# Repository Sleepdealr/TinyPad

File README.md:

# Tinypad 4x3 Macropad

Small & cheap 4x3 macropad with space for 2 rotary encoders

Has been prototyped once and small changes has been made

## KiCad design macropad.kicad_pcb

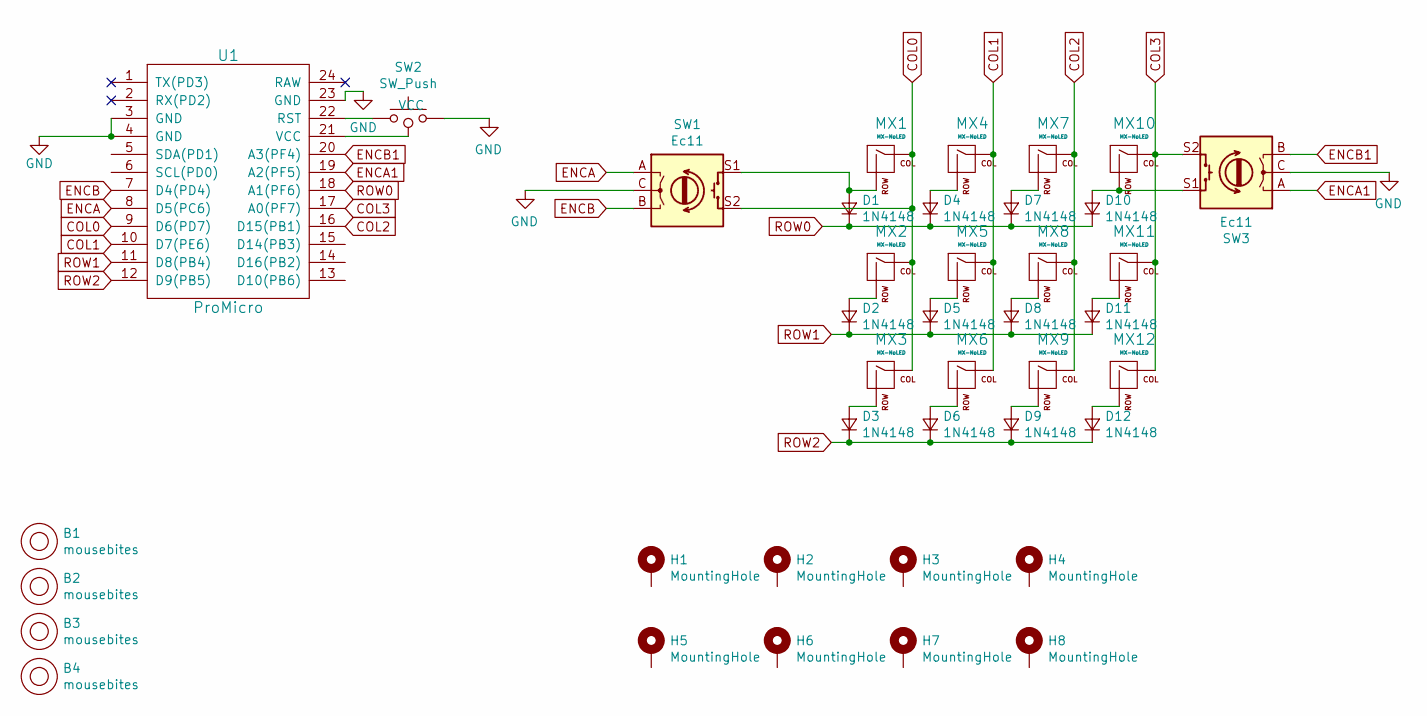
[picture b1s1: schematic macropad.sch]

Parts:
B1, B2, B3, B4: mousebites; breakaway-mousebites
D1, D2, D3, D4, D5, D6, D7, D8, D9, D10, D11, D12: 1N4148; D_DO-35_SOD27_P7.62mm_Horizontal
H1, H2, H3, H4, H5, H6, H7, H8: MountingHole; MountingHole_2.2mm_M2_Pad
MX1, MX2, MX3, MX4, MX5, MX6, MX7, MX8, MX9, MX10, MX11, MX12: MX-NoLED; MXOnly-1U-NoLED
SW1, SW3: Ec11; RotaryEncoder_Alps_EC11E-Switch_Vertical_H20mm
SW2: SW_Push; TACT_SWITCH_TVBP06
U1: ProMicro; ArduinoProMicro

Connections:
COL0: MX1.1 (COL), MX2.1 (COL), MX3.1 (COL), SW1.S2, U1.9 (D6(PD7))
COL1: MX4.1 (COL), MX5.1 (COL), MX6.1 (COL), U1.10 (D7(PE6))
COL2: MX7.1 (COL), MX8.1 (COL), MX9.1 (COL), U1.16 (D15(PB1))
COL3: MX10.1 (COL), MX11.1 (COL), MX12.1 (COL), SW3.S2, U1.17 (A0(PF7))
ENCA: SW1.A, U1.8 (D5(PC6))
ENCA1: SW3.A, U1.19 (A2(PF5))
ENCB: SW1.B, U1.7 (D4(PD4))
ENCB1: SW3.B, U1.20 (A3(PF4))
GND: SW1.C, SW2.1, SW3.C, U1.3 (GND), U1.4 (GND), U1.23 (GND)
unnamed: D1.2 (A), MX1.2 (ROW), SW1.S1
unnamed: D2.2 (A), MX2.2 (ROW)
unnamed: D3.2 (A), MX3.2 (ROW)
unnamed: D4.2 (A), MX4.2 (ROW)
unnamed: D5.2 (A), MX5.2 (ROW)
unnamed: D6.2 (A), MX6.2 (ROW)
unnamed: D7.2 (A), MX7.2 (ROW)
unnamed: D8.2 (A), MX8.2 (ROW)
unnamed: D9.2 (A), MX9.2 (ROW)
unnamed: D10.2 (A), MX10.2 (ROW), SW3.S1
unnamed: D11.2 (A), MX11.2 (ROW)
unnamed: D12.2 (A), MX12.2 (ROW)
unnamed: SW2.2, U1.22 (RST)
ROW0: D1.1 (K), D4.1 (K), D7.1 (K), D10.1 (K), U1.18 (A1(PF6))
ROW1: D2.1 (K), D5.1 (K), D8.1 (K), D11.1 (K), U1.11 (D8(PB4))
ROW2: D3.1 (K), D6.1 (K), D9.1 (K), D12.1 (K), U1.12 (D9(PB5))
VCC: U1.21 (VCC)

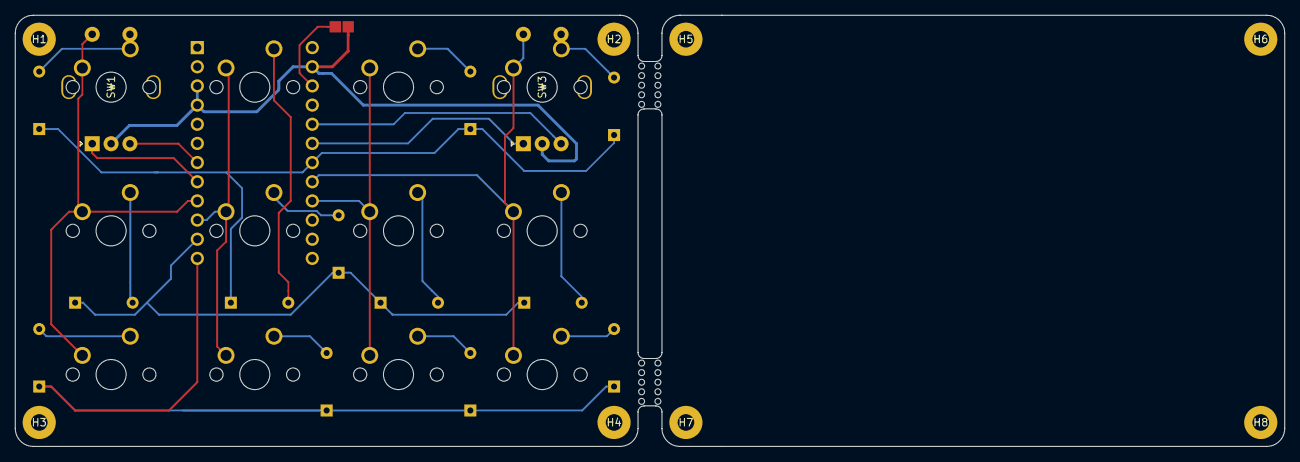
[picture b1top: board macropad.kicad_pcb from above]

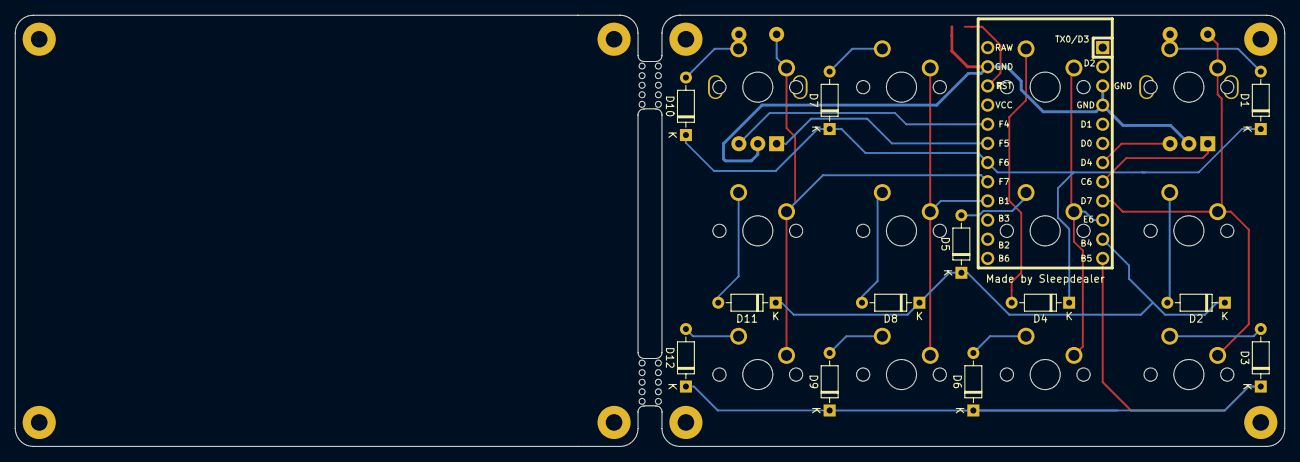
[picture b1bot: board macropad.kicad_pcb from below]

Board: 2 copper layers, 168.3 x 57.2 mm, 40 parts (12 on the bottom side), 25 nets.

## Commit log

2021-01-21 First attempt
2021-01-21 pcb overhaul
    Added second rotary encoder
    Moved Pro Micro under switches
    Made backplate
    Added artwork
    Made pcb smaller overall
    Added mousebites as symbol
2021-01-21 Created README.md
2021-01-22 Small fixes to PCB
    Rotated rotary encoders 180*
    Changed switch footprint to MX_Only
2021-01-23 Small placement adjustments
    Added credit
    Made diode placement more consistent
2021-02-25 Changed diode placement
2021-02-25 changed gitignore
2021-02-25 added to gitignore
